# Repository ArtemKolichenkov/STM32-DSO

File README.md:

# Digital storage oscilloscope using STM32
NOTE! Work in progress, the code has a lot of bugs and should not be used in production.

This project is based on STM32F429ZI microcontroller. Desktop client is written in Python, PCB layout is done in KiCad.
Code will be updated gradually and I will notify when the stable version is released.

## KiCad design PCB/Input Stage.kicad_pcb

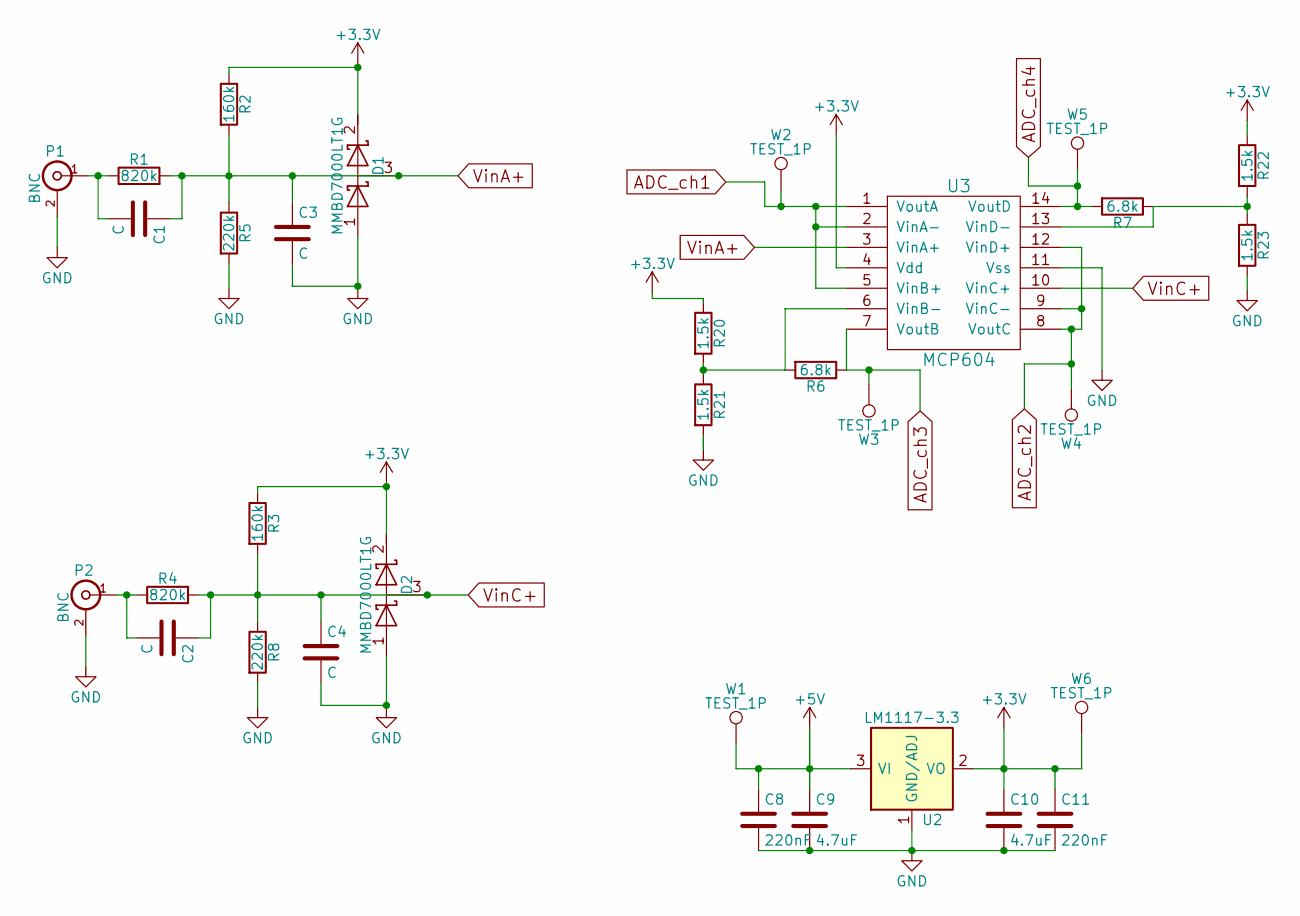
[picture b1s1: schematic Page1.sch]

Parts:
C1, C2, C3, C4: C; C_0805_HandSoldering
C8, C11: 220nF; C_0805_HandSoldering
C9, C10: 4.7uF; CP_Tantalum_Case-A_EIA-3216-18_Hand
D1, D2: MMBD7000LT1G; SOT-23
P1, P2: BNC; BNC_Socket_TYCO-AMP_LargePads
R1, R4: 820k; R_1206_HandSoldering
R2, R3: 160k; R_1206_HandSoldering
R5, R8: 220k; R_1206_HandSoldering
R6, R7: 6.8k; R_1206_HandSoldering
R20, R21, R22, R23: 1.5k; R_1206_HandSoldering
U2: LM1117-3.3; SOT-223
U3: MCP604; SOIC-14_N
W1, W2, W3, W4, W5, W6: TEST_1P; Measurement_Point_Round-SMD-Pad_Big

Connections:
+5V: C8.1, C9.1, U2.3 (VI), W1.1; also elsewhere on the board
ADC_ch1: U3.1 (VoutA), U3.2 (VinA-), U3.5 (VinB+), W2.1; also elsewhere on the board
ADC_ch2: U3.8 (VoutC), U3.9 (VinC-), U3.12 (VinD+), W4.1; also elsewhere on the board
ADC_ch3: R6.1, U3.7 (VoutB), W3.1; also elsewhere on the board
ADC_ch4: R7.2, U3.14 (VoutD), W5.1; also elsewhere on the board
GND: C3.2, C4.2, C8.2, C9.2, C10.2, C11.2, D1.1 (A), D2.1 (A), P1.2 (Ext), P2.2 (Ext), R5.2, R8.2, R21.2, R23.2, U2.1 (GND/ADJ), U3.11 (Vss); also elsewhere on the board
unnamed: C1.2, P1.1 (In), R1.1
unnamed: C2.2, P2.1 (In), R4.1
unnamed: R6.2, R20.2, R21.1, U3.6 (VinB-)
unnamed: R7.1, R22.2, R23.1, U3.13 (VinD-)
VBAT: C10.1, C11.1, D1.2 (K), D2.2 (K), R2.1, R3.1, R20.1, R22.1, U2.2 (VO), U2.4 (VO), U3.4 (Vdd), W6.1; also elsewhere on the board
VinA+: C1.1, C3.1, D1.3 (common), R1.2, R2.2, R5.1, U3.3 (VinA+)
VinC+: C2.1, C4.1, D2.3 (common), R3.2, R4.2, R8.1, U3.10 (VinC+)

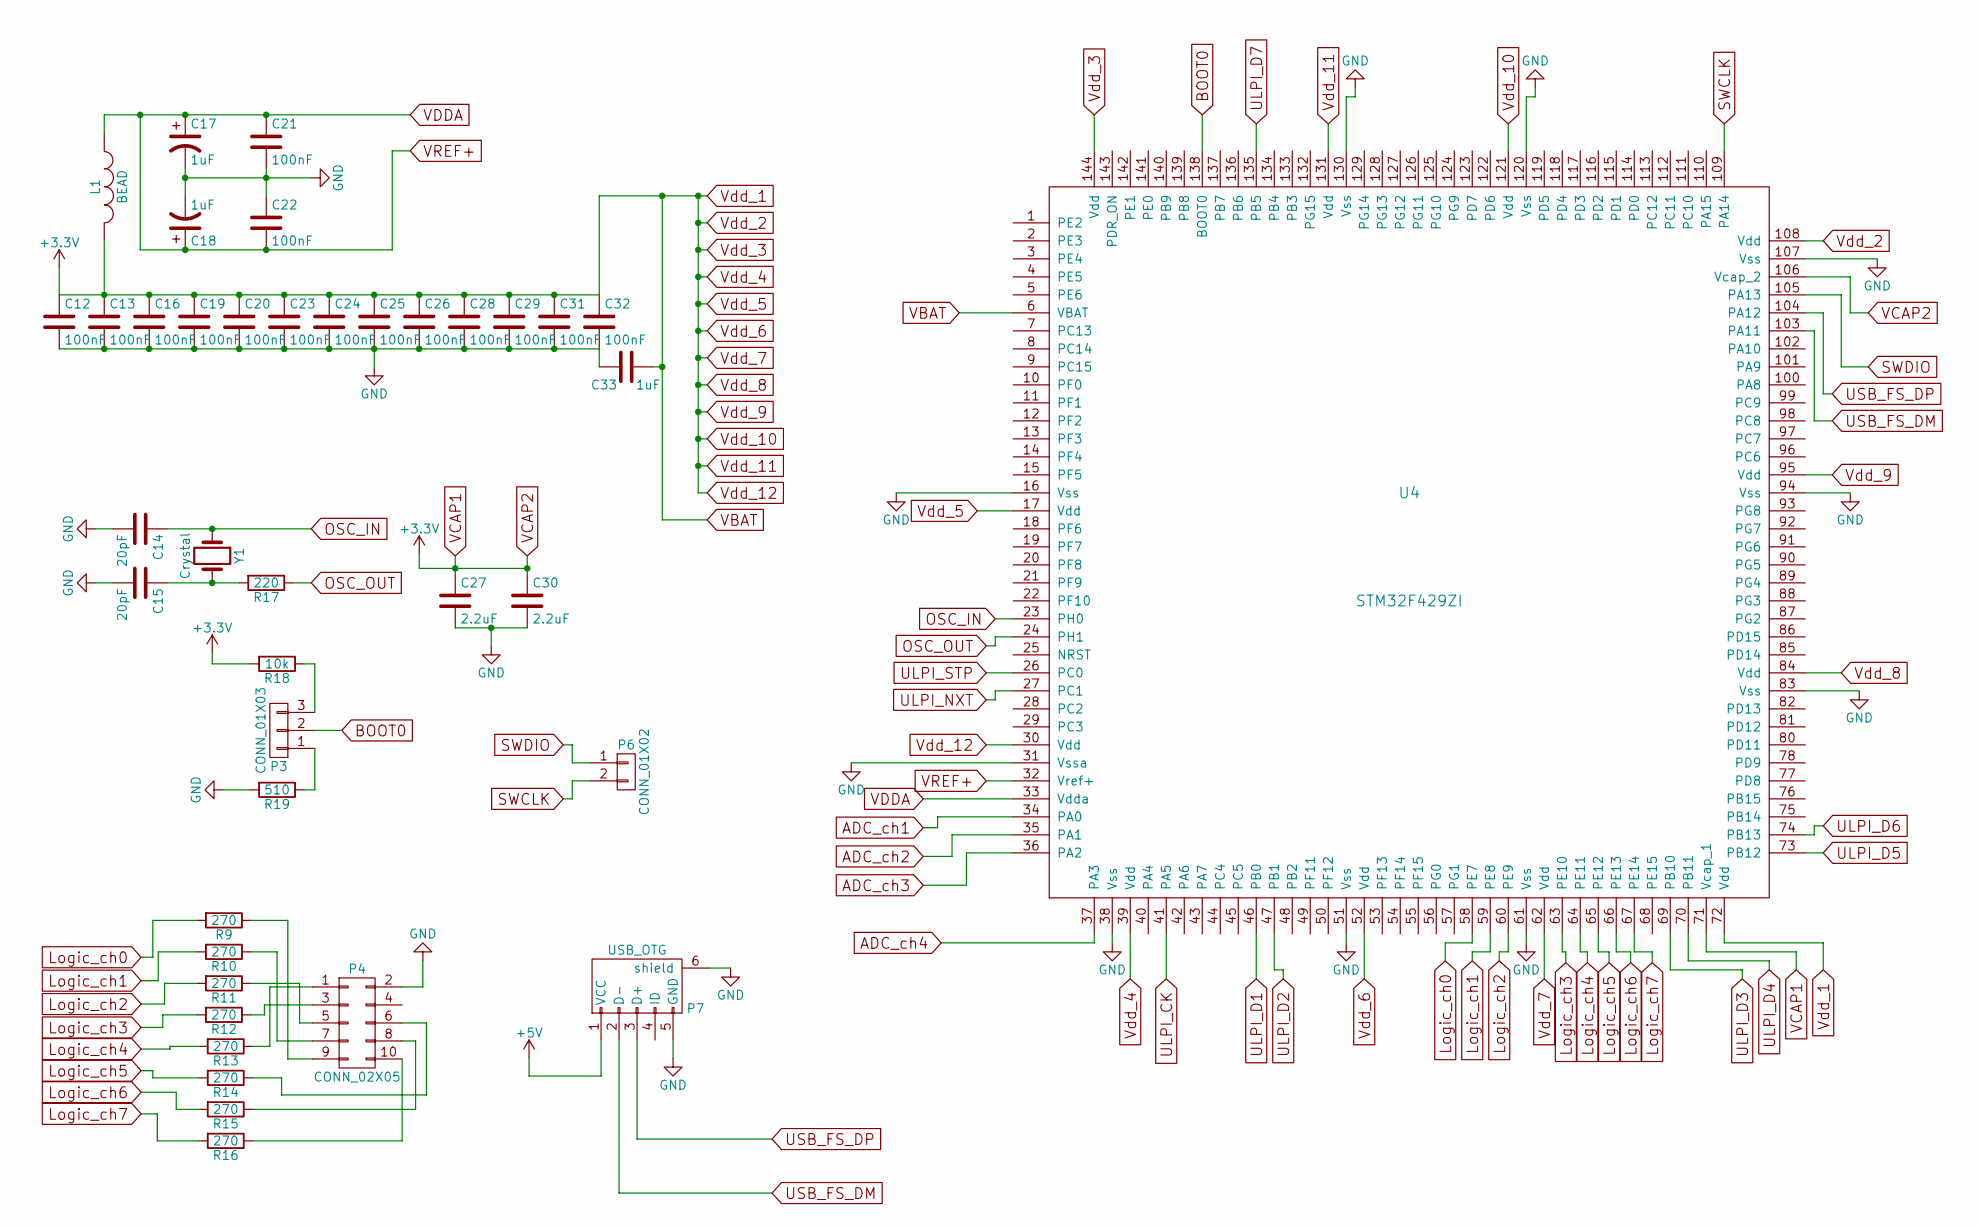
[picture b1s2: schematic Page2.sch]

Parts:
C12, C13, C16, C19, C20, C21, C22, C23, C24, C25, C26, C28, C29, C31, C32: 100nF; C_0805_HandSoldering
C14, C15: 20pF; C_0805_HandSoldering
C17, C18: 1uF; CP_Tantalum_Case-A_EIA-3216-18_Hand
C27, C30: 2.2uF; C_0805_HandSoldering
C33: 1uF; C_0805_HandSoldering
L1: BEAD; C_1210_HandSoldering
P3: CONN_01X03; Pin_Header_Straight_1x03_Pitch2.54mm
P4: CONN_02X05; IDC_Header_Straight_10pins
P6: CONN_01X02; Pin_Header_Straight_1x02_Pitch2.54mm
P7: USB_OTG; USB_Mini-B
R9, R10, R11, R12, R13, R14, R15, R16: 270; R_1206_HandSoldering
R17: 220; R_1206_HandSoldering
R18: 10k; R_1206_HandSoldering
R19: 510; R_1206_HandSoldering
U4: STM32F429ZI; LQFP-144_20x20mm_Pitch0.5mm
Y1: Crystal; Crystal_SMD_HC49-SD_HandSoldering

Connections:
+5V: P7.1 (VCC); also elsewhere on the board
ADC_ch1: U4.34 (PA0); also elsewhere on the board
ADC_ch2: U4.35 (PA1); also elsewhere on the board
ADC_ch3: U4.36 (PA2); also elsewhere on the board
ADC_ch4: U4.37 (PA3); also elsewhere on the board
BOOT0: P3.2, U4.138 (BOOT0)
GND: C12.2, C13.2, C14.2, C15.2, C16.2, C17.2, C18.2, C19.2, C20.2, C21.2, C22.1, C23.2, C24.2, C25.2, C26.2, C27.2, C28.2, C29.2, C30.2, C31.2, C32.2, C33.2, P4.2, P7.5 (GND), P7.6 (shield), R19.2, U4.16 (Vss), U4.31 (Vssa), U4.38 (Vss), U4.51 (Vss), U4.61 (Vss), U4.83 (Vss), U4.94 (Vss), U4.107 (Vss), U4.120 (Vss), U4.130 (Vss); also elsewhere on the board
Logic_ch0: R9.2, U4.58 (PE7)
Logic_ch1: R10.2, U4.59 (PE8)
Logic_ch2: R11.2, U4.60 (PE9)
Logic_ch3: R12.2, U4.63 (PE10)
Logic_ch4: R13.2, U4.64 (PE11)
Logic_ch5: R14.2, U4.65 (PE12)
Logic_ch6: R15.2, U4.66 (PE13)
Logic_ch7: R16.2, U4.67 (PE14)
unnamed: C15.1, R17.2, Y1.2
unnamed: P3.1, R19.1
unnamed: P3.3, R18.1
unnamed: P4.1, R13.1
unnamed: P4.3, R12.1
unnamed: P4.5, R11.1
unnamed: P4.6, R14.1
unnamed: P4.7, R10.1
unnamed: P4.8, R15.1
unnamed: P4.9, R9.1
unnamed: P4.10, R16.1
OSC_IN: C14.1, U4.23 (PH0), Y1.1
OSC_OUT: R17.1, U4.24 (PH1)
SWCLK: P6.2, U4.109 (PA14)
SWDIO: P6.1, U4.105 (PA13)
ULPI_CK: U4.41 (PA5)
ULPI_D1: U4.46 (PB0)
ULPI_D2: U4.47 (PB1)
ULPI_D3: U4.69 (PB10)
ULPI_D4: U4.70 (PB11)
ULPI_D5: U4.73 (PB12)
ULPI_D6: U4.74 (PB13)
ULPI_D7: U4.135 (PB5)
ULPI_NXT: U4.27 (PC1)
ULPI_STP: U4.26 (PC0)
USB_FS_DM: P7.2 (D-), U4.103 (PA11)
USB_FS_DP: P7.3 (D+), U4.104 (PA12)
VBAT: C12.1, C13.1, C16.1, C19.1, C20.1, C23.1, C24.1, C25.1, C26.1, C27.1, C28.1, C29.1, C30.1, C31.1, C32.1, C33.1, L1.2, R18.2, U4.6 (VBAT), U4.17 (Vdd), U4.30 (Vdd), U4.39 (Vdd), U4.52 (Vdd), U4.62 (Vdd), U4.71 (Vcap_1), U4.72 (Vdd), U4.84 (Vdd), U4.95 (Vdd), U4.106 (Vcap_2), U4.108 (Vdd), U4.121 (Vdd), U4.131 (Vdd), U4.144 (Vdd); also elsewhere on the board
VDDA: C17.1, C18.1, C21.1, C22.2, L1.1, U4.32 (Vref+), U4.33 (Vdda)

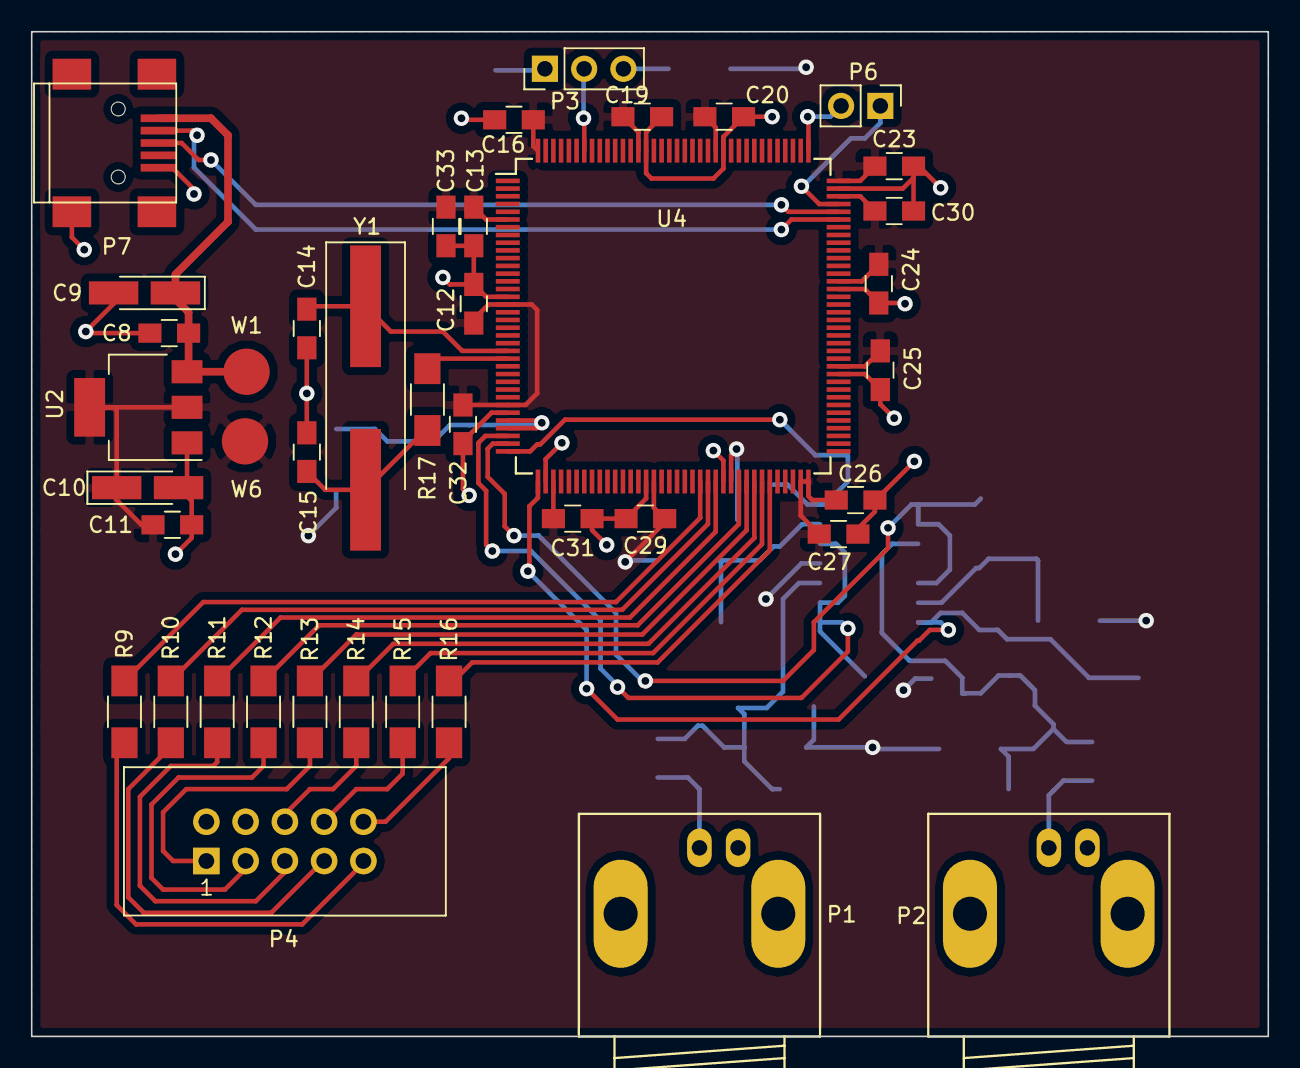
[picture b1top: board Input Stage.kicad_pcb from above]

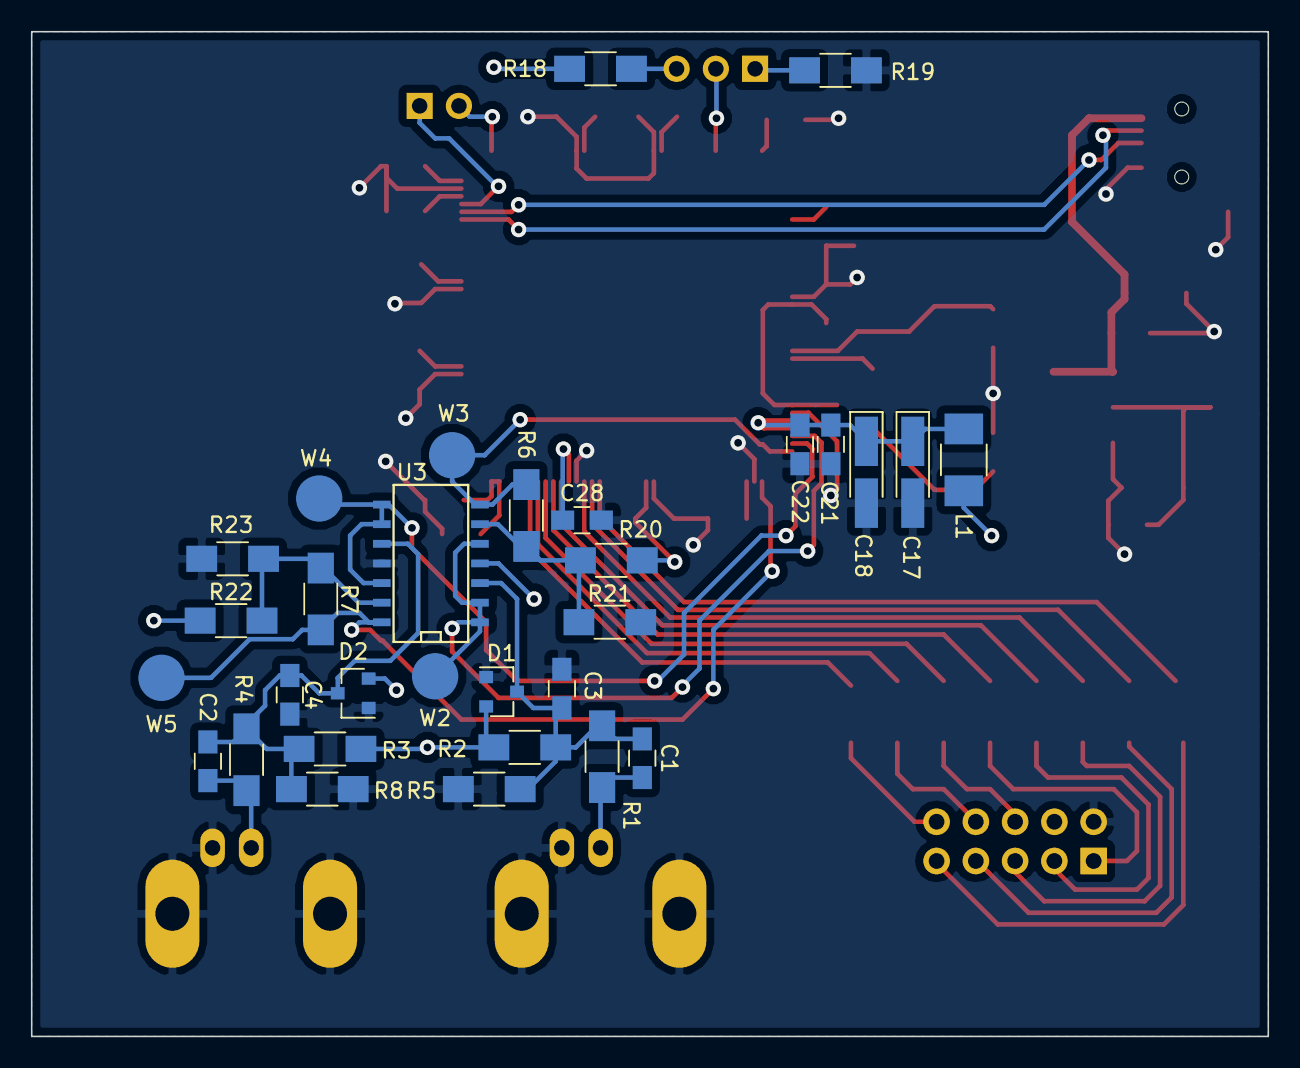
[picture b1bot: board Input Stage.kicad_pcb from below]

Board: 2 copper layers, 80.0 x 65.0 mm, 72 parts (31 on the bottom side), 40 nets.

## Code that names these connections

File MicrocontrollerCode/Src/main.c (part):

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  __HAL_RCC_GPIOE_CLK_ENABLE();
	

  /*Configure GPIO pins : PE7 PE8 PE9 PE10 
                           PE11 PE12 PE13 PE14 */
  GPIO_InitStruct.Pin = GPIO_PIN_7|GPIO_PIN_8|GPIO_PIN_9|GPIO_PIN_10 
                          |GPIO_PIN_11|GPIO_PIN_12|GPIO_PIN_13|GPIO_PIN_14;
  GPIO_InitStruct.Mode = GPIO_MODE_INPUT;
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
